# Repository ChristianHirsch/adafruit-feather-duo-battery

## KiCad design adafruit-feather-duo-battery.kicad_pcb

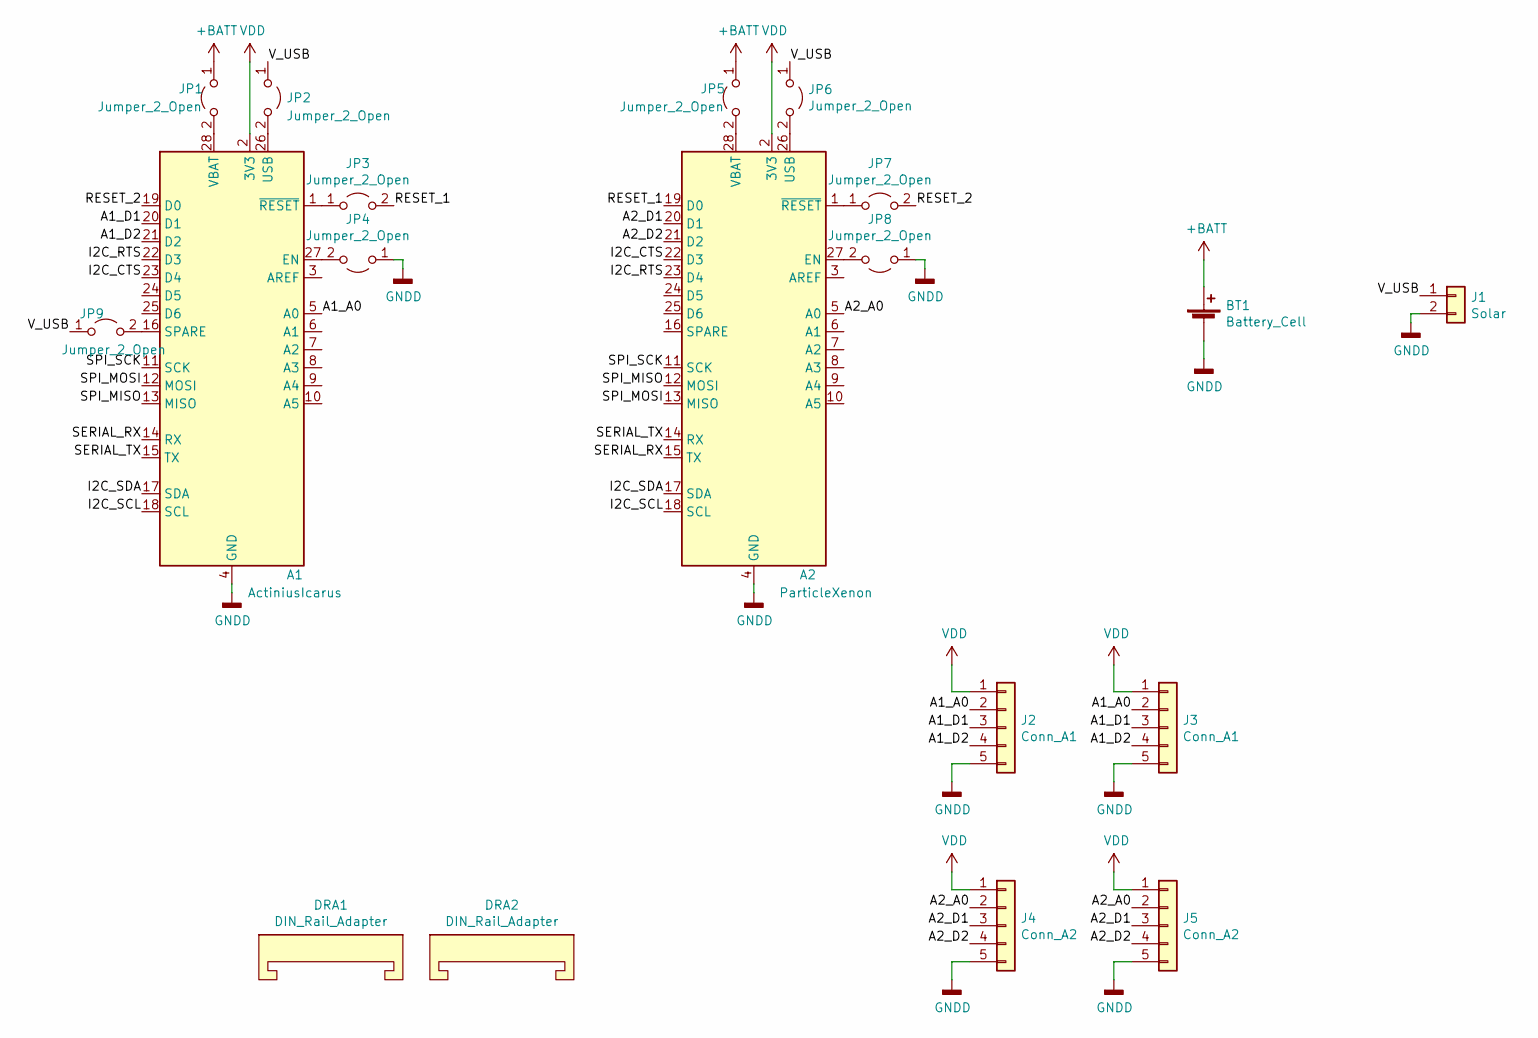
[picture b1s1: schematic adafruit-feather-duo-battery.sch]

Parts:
A1: ActiniusIcarus; Adafruit_Feather
A2: ParticleXenon; Adafruit_Feather
BT1: Battery_Cell; BatteryHolder_Keystone_1042_1x18650
DRA1, DRA2: DIN_Rail_Adapter; DINRailAdapter_3xM3_PhoenixContact_1201578
J1: Solar; TerminalBlock_bornier-2_P5.08mm
J2: Conn_A1; PinHeader_1x05_P2.54mm_Vertical
J3: Conn_A1; TerminalBlock_bornier-5_P5.08mm
J4: Conn_A2; PinHeader_1x05_P2.54mm_Vertical
J5: Conn_A2; TerminalBlock_bornier-5_P5.08mm
JP1, JP2, JP3, JP4, JP5, JP6, JP7, JP8, JP9: Jumper_2_Open; PinHeader_1x02_P2.54mm_Vertical

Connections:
+BATT: BT1.1 (+), JP1.1 (A), JP5.1 (A)
/A1_A0: A1.5 (A0), J2.2, J3.2
/A1_D1: A1.20 (D1), J2.3, J3.3
/A1_D2: A1.21 (D2), J2.4, J3.4
/A2_A0: A2.5 (A0), J4.2, J5.2
/A2_D1: A2.20 (D1), J4.3, J5.3
/A2_D2: A2.21 (D2), J4.4, J5.4
/I2C_CTS: A1.23 (D4), A2.22 (D3)
/I2C_RTS: A1.22 (D3), A2.23 (D4)
/I2C_SCL: A1.18 (SCL), A2.18 (SCL)
/I2C_SDA: A1.17 (SDA), A2.17 (SDA)
/RESET_1: A2.19 (D0), JP3.2 (B)
/RESET_2: A1.19 (D0), JP7.2 (B)
/SERIAL_RX: A1.14 (RX), A2.15 (TX)
/SERIAL_TX: A1.15 (TX), A2.14 (RX)
/SPI_MISO: A1.13 (MISO), A2.12 (MOSI)
/SPI_MOSI: A1.12 (MOSI), A2.13 (MISO)
/SPI_SCK: A1.11 (SCK), A2.11 (SCK)
/V_USB: J1.1, JP2.1 (A), JP6.1 (A), JP9.1 (A)
GNDD: A1.4 (GND), A2.4 (GND), BT1.2 (-), J1.2, J2.5, J3.5, J4.5, J5.5, JP4.1 (A), JP8.1 (A)
unnamed: A1.1 (~RESET), JP3.1 (A)
unnamed: A1.16 (SPARE), JP9.2 (B)
unnamed: A1.26 (USB), JP2.2 (B)
unnamed: A1.27 (EN), JP4.2 (B)
unnamed: A1.28 (VBAT), JP1.2 (B)
unnamed: A2.1 (~RESET), JP7.1 (A)
unnamed: A2.26 (USB), JP6.2 (B)
unnamed: A2.27 (EN), JP8.2 (B)
unnamed: A2.28 (VBAT), JP5.2 (B)
VDD: A1.2 (3V3), A2.2 (3V3), J2.1, J3.1, J4.1, J5.1

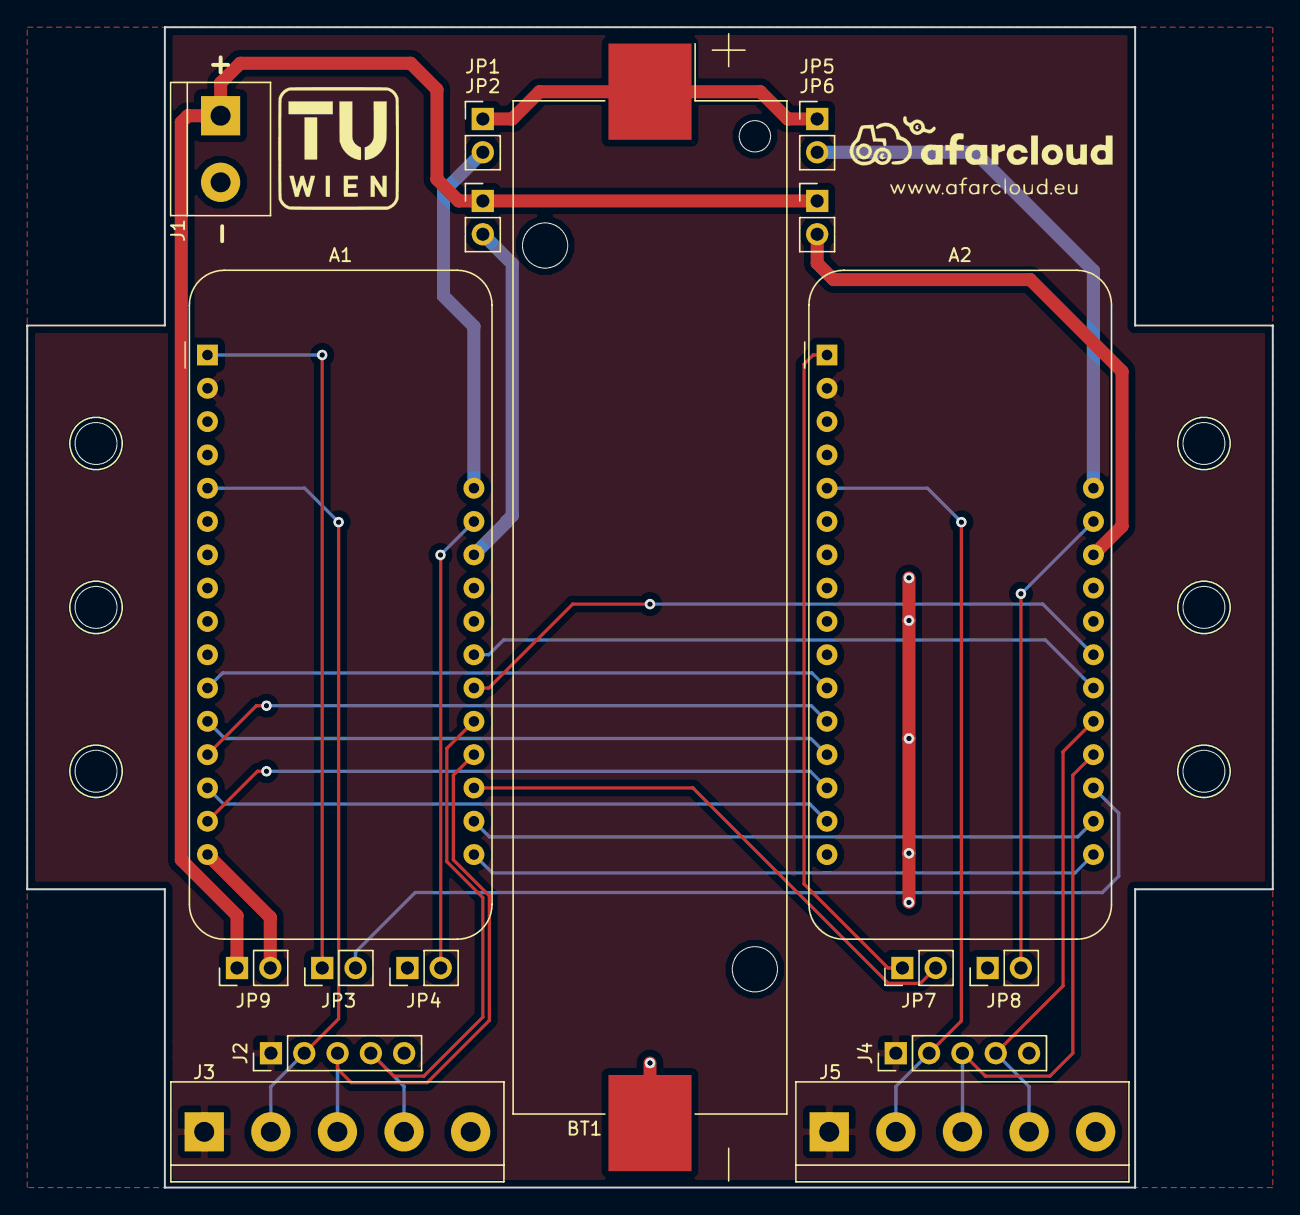
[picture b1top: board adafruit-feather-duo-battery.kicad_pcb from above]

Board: 2 copper layers, 95.0 x 88.5 mm, 19 parts (0 on the bottom side), 30 nets.
